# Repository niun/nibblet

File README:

Nibblet is not ready yet. It will be a binary coded decimal LED wrist watch where some LEDs are acting as light sensors for enabling touch-guesture control.

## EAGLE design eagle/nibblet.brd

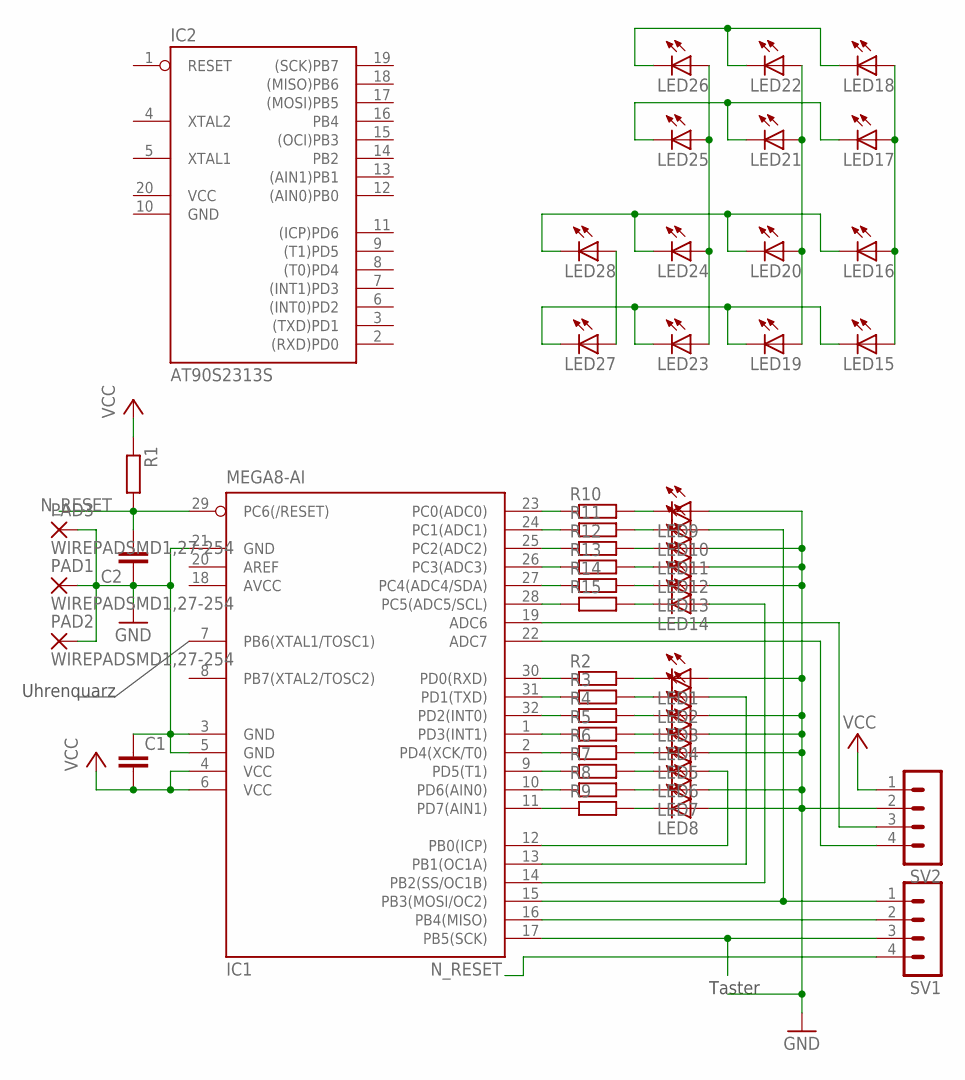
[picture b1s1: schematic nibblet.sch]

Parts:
C1, C2: C-EUC1206; C1206
IC1: MEGA8-AI; TQFP32-08
IC2: AT90S2313S; SO20L
LED1, LED2, LED3, LED4, LED5, LED6, LED7, LED8, LED9, LED10, LED11, LED12, LED13, LED14, LED15, LED16, LED17, LED18, LED19, LED20, LED21, LED22, LED23, LED24, LED25, LED26, LED27, LED28: LEDCHIP-LED0805; CHIP-LED0805
PAD1, PAD2, PAD3: WIREPADSMD1,27-254; SMD1,27-2,54
R1: R-EU_M1206; M1206
R2, R3, R4, R5, R6, R7, R8, R9, R10, R11, R12, R13, R14, R15: R-EU_R0805; R0805
SV1, SV2: MA04-1

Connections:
AVCC: IC1.18 (AVCC)
GND: C1.1, C2.1, IC1.3 (GND), IC1.5 (GND), IC1.21 (GND), IC2.10 (GND), LED1.A, LED3.A, LED4.A, LED5.A, LED7.A, LED8.A, LED9.A, LED11.A, LED12.A, LED13.A, PAD1.1, PAD2.1, PAD3.1, SV2.2
unnamed: IC1.25 (PC2(ADC2)), R12.1
unnamed: LED11.C, R12.2
unnamed: IC1.23 (PC0(ADC0)), R10.1
unnamed: IC1.24 (PC1(ADC1)), R11.1
unnamed: IC1.26 (PC3(ADC3)), R13.1
unnamed: LED12.C, R13.2
unnamed: IC1.27 (PC4(ADC4/SDA)), R14.1
unnamed: IC1.30 (PD0(RXD)), R2.1
unnamed: IC1.31 (PD1(TXD)), R3.1
unnamed: IC1.32 (PD2(INT0)), R4.1
unnamed: IC1.1 (PD3(INT1)), R5.1
unnamed: IC1.2 (PD4(XCK/T0)), R6.1
unnamed: IC1.9 (PD5(T1)), R7.1
unnamed: IC1.10 (PD6(AIN0)), R8.1
unnamed: IC1.15 (PB3(MOSI/OC2)), LED10.A, SV1.1
unnamed: IC1.22 (ADC7), SV2.4
unnamed: IC1.11 (PD7(AIN1)), R9.1
unnamed: LED8.C, R9.2
unnamed: IC1.19 (ADC6), SV2.3
unnamed: IC1.14 (PB2(SS/OC1B)), LED14.A
unnamed: IC1.17 (PB5(SCK)), SV1.3
unnamed: IC1.13 (PB1(OC1A)), LED2.A
unnamed: IC1.12 (PB0(ICP)), LED6.A
unnamed: IC1.16 (PB4(MISO)), SV1.2
unnamed: LED7.C, R8.2
unnamed: LED6.C, R7.2
unnamed: LED5.C, R6.2
unnamed: LED4.C, R5.2
unnamed: LED3.C, R4.2
unnamed: LED2.C, R3.2
unnamed: LED1.C, R2.2
unnamed: LED13.C, R14.2
unnamed: IC1.28 (PC5(ADC5/SCL)), R15.1
unnamed: LED14.C, R15.2
unnamed: LED10.C, R11.2
unnamed: LED9.C, R10.2
unnamed: LED15.C, LED19.C, LED23.C, LED27.C
unnamed: LED27.A, LED28.A
unnamed: LED23.A, LED24.A, LED25.A, LED26.A
unnamed: LED19.A, LED20.A, LED21.A, LED22.A
unnamed: LED15.A, LED16.A, LED17.A, LED18.A
unnamed: LED16.C, LED20.C, LED24.C, LED28.C
unnamed: LED17.C, LED21.C, LED25.C
unnamed: LED18.C, LED22.C, LED26.C
N_RESET: C2.2, IC1.29 (PC6(/RESET)), R1.2, SV1.4
VCC: C1.2, IC1.4 (VCC), IC1.6 (VCC), IC2.20 (VCC), R1.1, SV2.1

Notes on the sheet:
Uhrenquarz
Taster

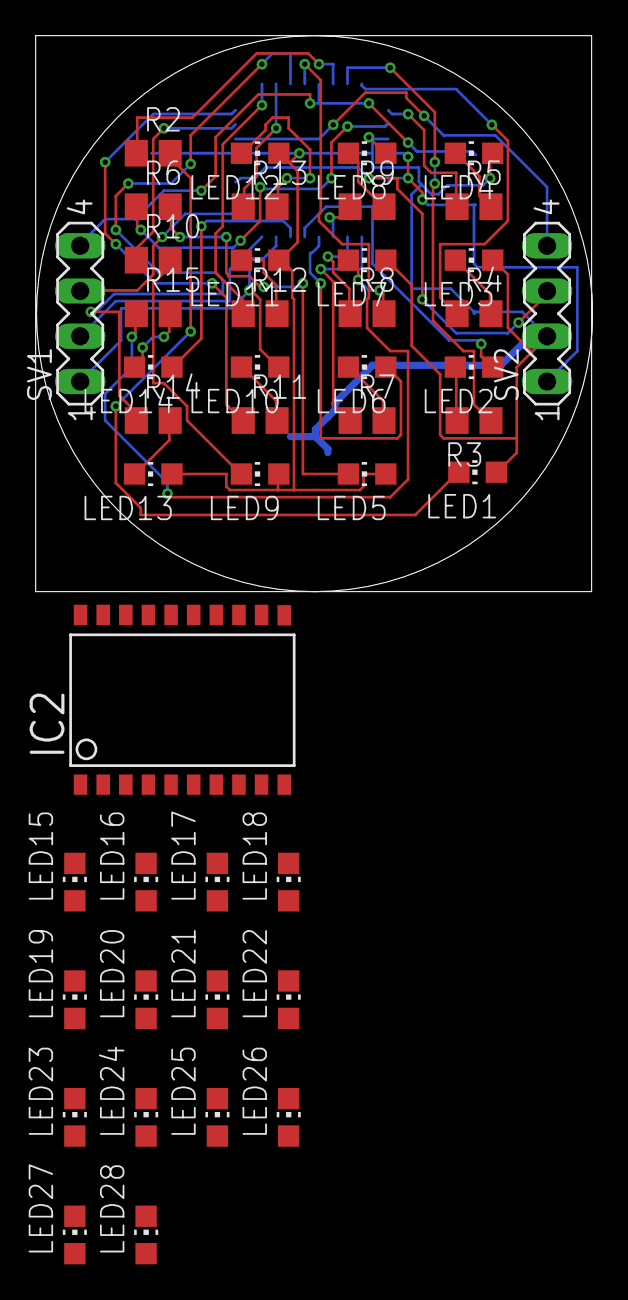
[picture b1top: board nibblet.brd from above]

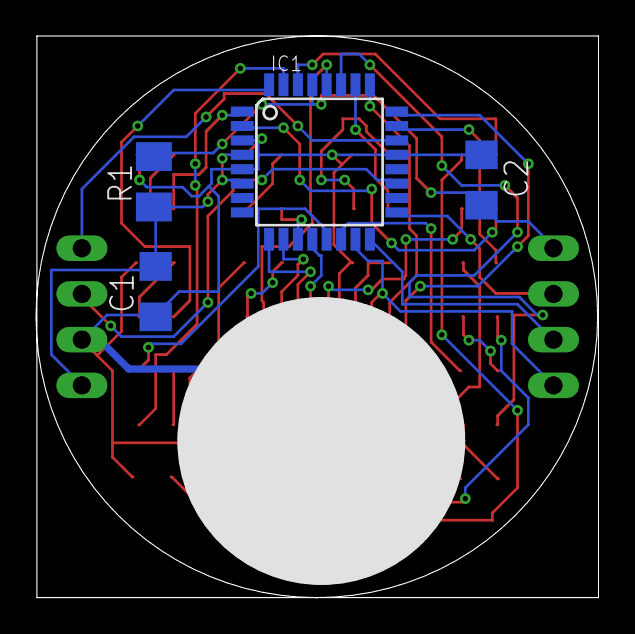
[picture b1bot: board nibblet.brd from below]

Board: 2 copper layers, 31.3 x 31.2 mm, 52 parts (7 on the bottom side), 47 nets.

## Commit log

2011-03-11 First commit. Essential eagle files added.
2013-02-19 after long project idle time
2013-02-19 add autorouter battery restrict, leiton designrules
2013-02-22 add series resistors to leds
2013-02-22 placed resistors and autorouted 100%
2013-02-22 consistent led order
2013-02-22 led position really consistent
2013-06-18 eagle project config
2013-12-29 pad for battery. GND on the PCB??
2014-01-07 pin checking, LED array
